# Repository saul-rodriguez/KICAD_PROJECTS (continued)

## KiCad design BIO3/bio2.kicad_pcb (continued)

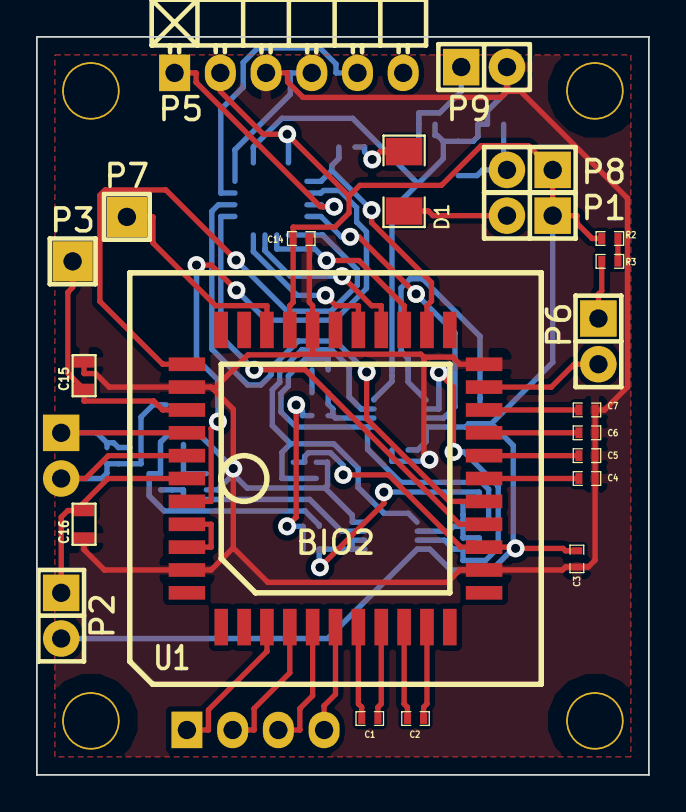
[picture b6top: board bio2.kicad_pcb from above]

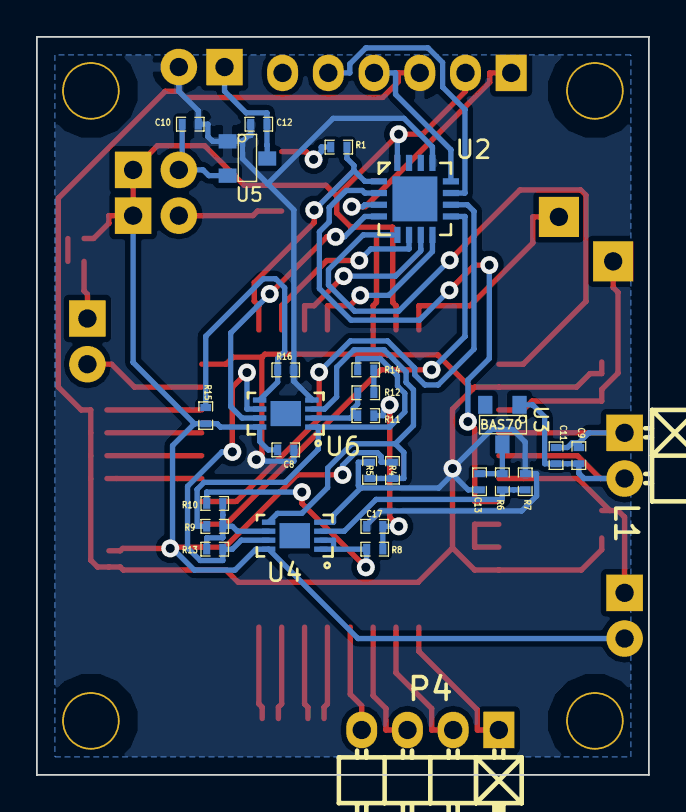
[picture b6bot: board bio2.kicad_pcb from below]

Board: 2 copper layers, 34.0 x 41.0 mm, 50 parts (28 on the bottom side), 50 nets.

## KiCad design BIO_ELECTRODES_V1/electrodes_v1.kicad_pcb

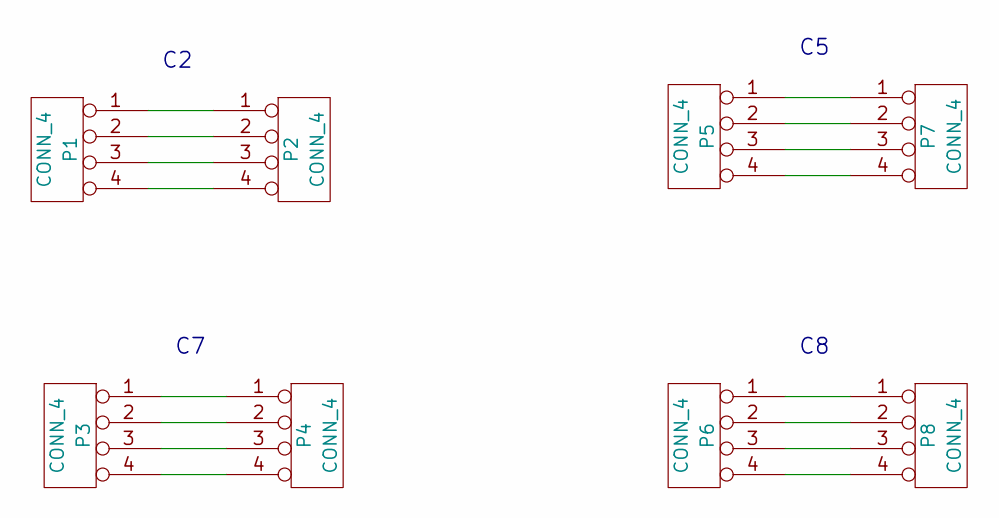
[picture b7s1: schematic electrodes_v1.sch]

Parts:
P1, P2, P3, P4, P5, P6, P7, P8: CONN_4

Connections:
unnamed: P3.1, P4.1
unnamed: P3.2, P4.2
unnamed: P3.3, P4.3
unnamed: P3.4, P4.4
unnamed: P6.1, P8.1
unnamed: P6.2, P8.2
unnamed: P6.3, P8.3
unnamed: P6.4, P8.4
unnamed: P1.1, P2.1
unnamed: P1.2, P2.2
unnamed: P1.3, P2.3
unnamed: P1.4, P2.4
unnamed: P5.1, P7.1
unnamed: P5.2, P7.2
unnamed: P5.3, P7.3
unnamed: P5.4, P7.4

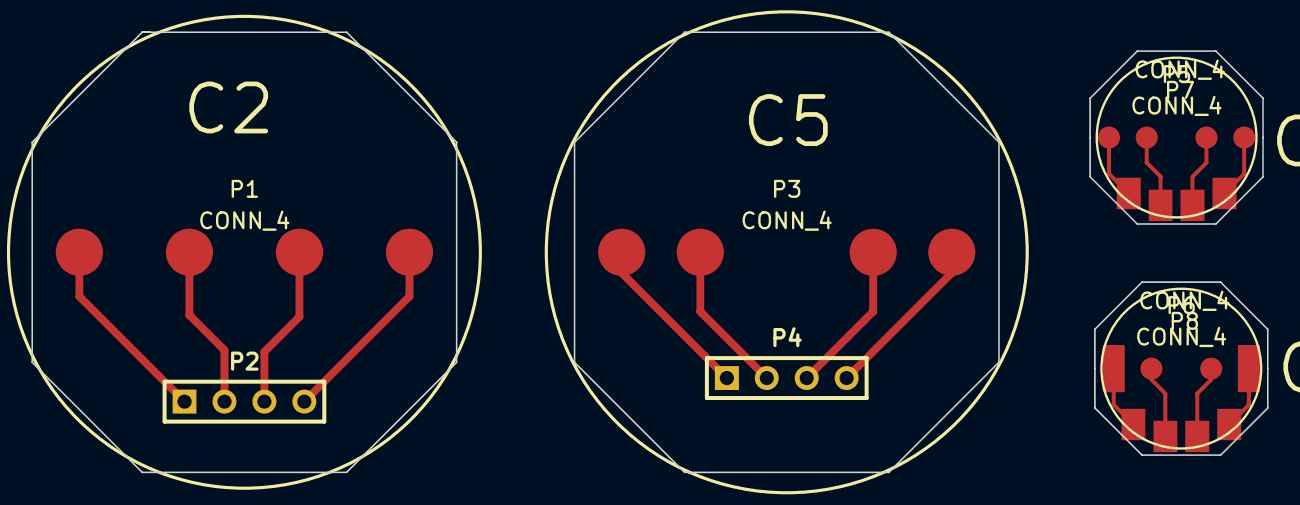
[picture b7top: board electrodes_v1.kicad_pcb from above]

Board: 2 copper layers, 78.6 x 28.0 mm, 8 parts (0 on the bottom side), 16 nets.

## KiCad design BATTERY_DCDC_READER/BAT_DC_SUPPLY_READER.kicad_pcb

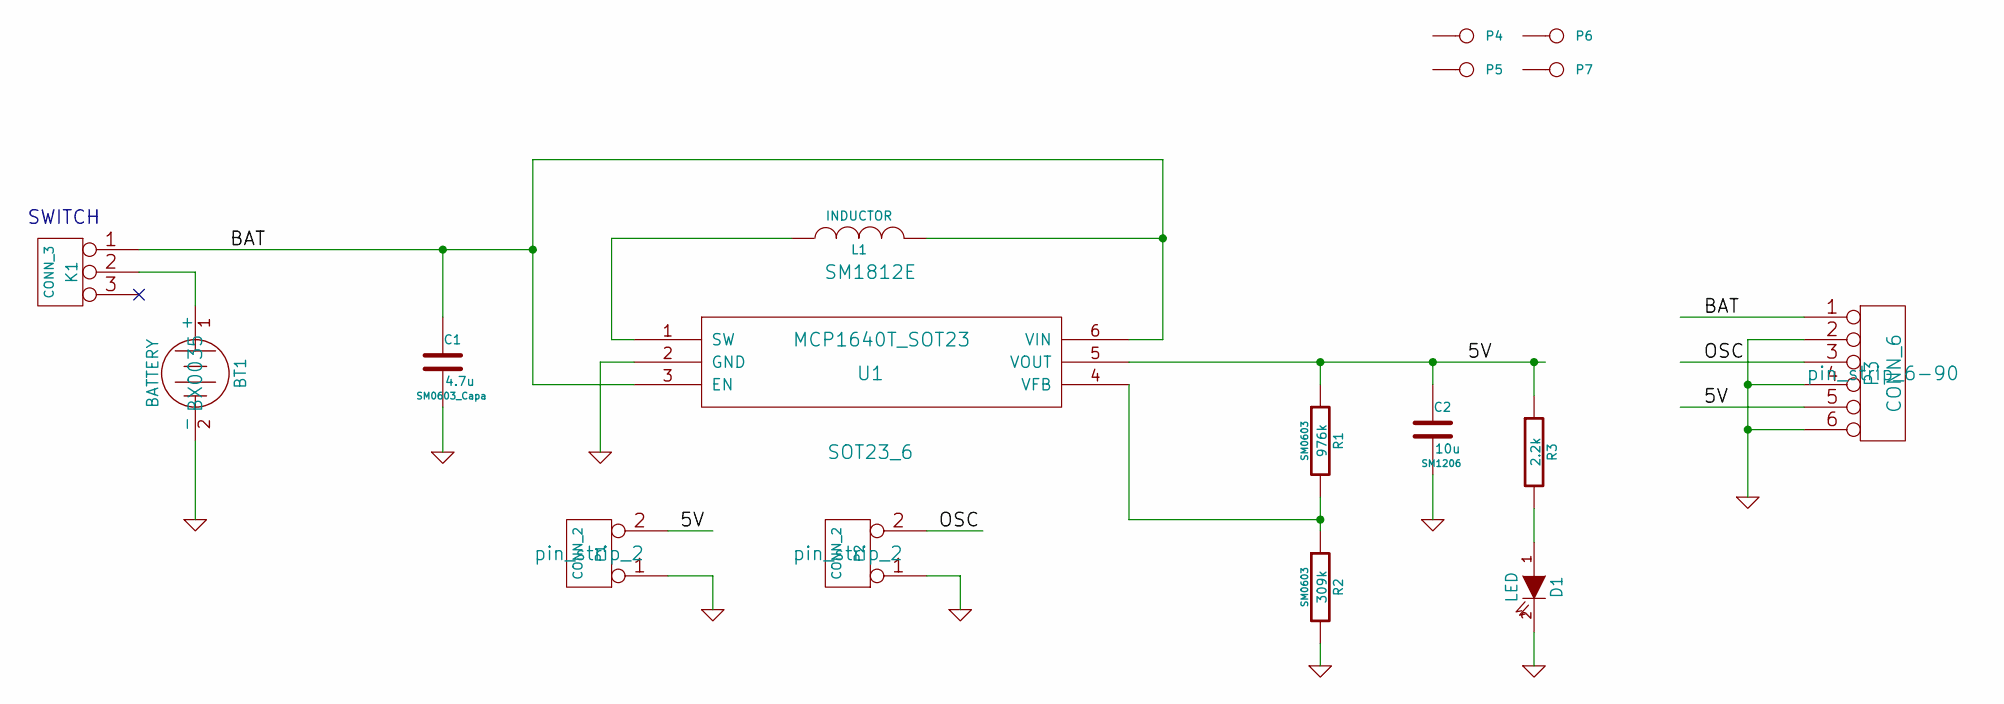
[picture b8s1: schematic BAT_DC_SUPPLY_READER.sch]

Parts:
BT1: BATTERY; BX0035
C1: 4.7u; SM0603_Capa
C2: 10u; SM1206
D1: LED
K1: CONN_3
L1: INDUCTOR; SM1812E
P1, P2: CONN_2; pin_strip_2
P3: CONN_6; pin_strip_6-90
P4, P5, P6, P7: CONN_1
R1: 976k; SM0603
R2: 309k; SM0603
R3: 2.2k
U1: MCP1640T_SOT23; SOT23_6

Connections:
/5V: C2.1, P1.2 (PM), P3.5, R1.1, R3.1, U1.5 (VOUT)
/BAT: C1.1, K1.1, L1.2, P3.1, U1.3 (EN), U1.6 (VIN)
/OSC: P2.2 (PM), P3.3
GND: BT1.2 (-), C1.2, C2.2, D1.2 (K), P1.1, P2.1, P3.2, P3.4, P3.6, R2.2, U1.2 (GND)
unnamed: BT1.1 (+), K1.2 (PM)
unnamed: D1.1 (A), R3.2
unnamed: L1.1, U1.1 (SW)
unnamed: R1.2, R2.1, U1.4 (VFB)

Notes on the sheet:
SWITCH

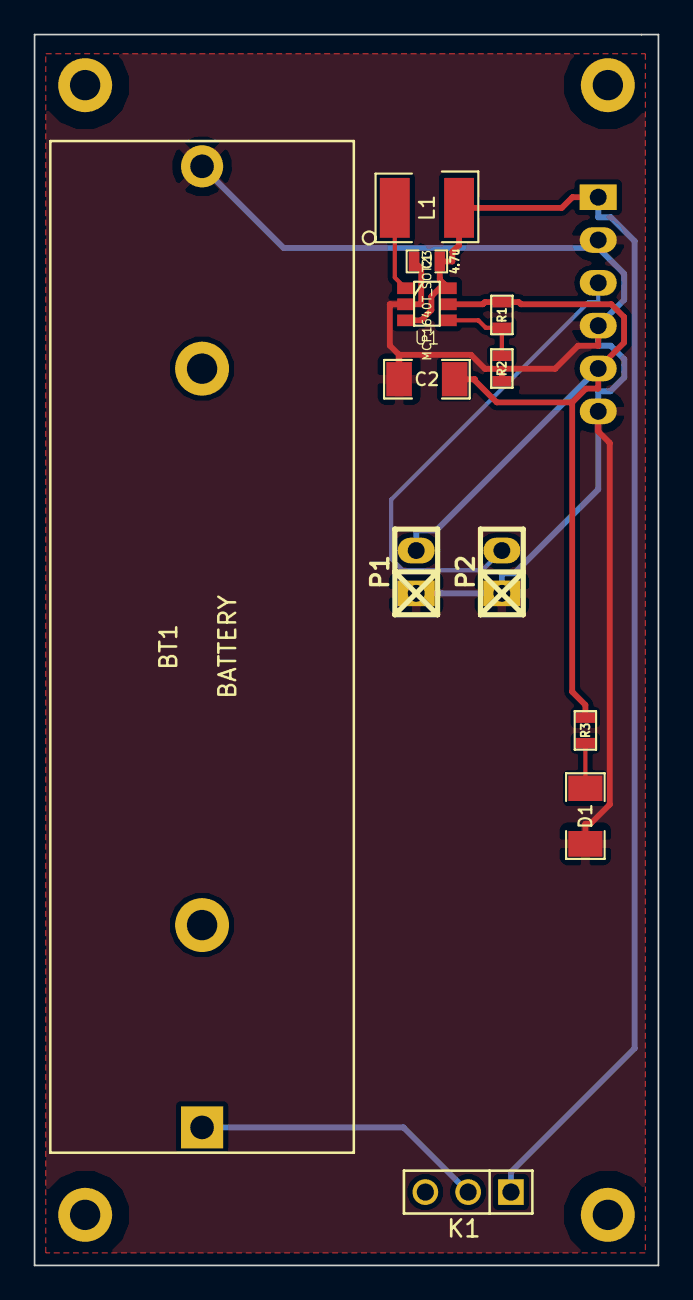
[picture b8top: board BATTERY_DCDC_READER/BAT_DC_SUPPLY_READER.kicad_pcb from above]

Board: 2 copper layers, 37.0 x 73.0 mm, 17 parts (1 on the bottom side), 8 nets.
